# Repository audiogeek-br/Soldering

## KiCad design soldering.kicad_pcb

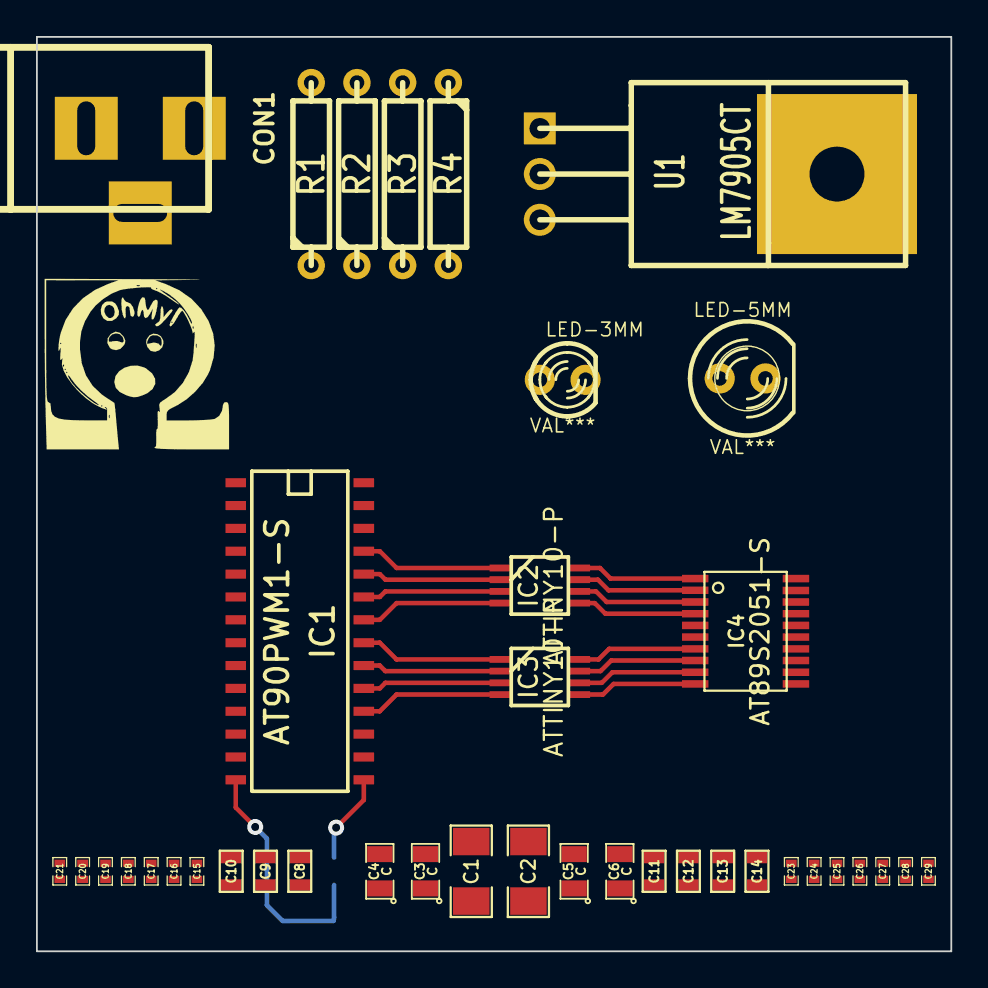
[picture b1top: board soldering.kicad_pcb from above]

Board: 2 copper layers, 50.8 x 50.8 mm, 40 parts (1 on the bottom side), 18 nets.

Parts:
C1, C2: C; SM1206
C3, C4, C5, C6: C; SM0805
C7, C8, C9, C10, C11, C12, C13, C14: C; SM0603
C15, C16, C17, C18, C19, C20, C21, C23, C24, C25, C26, C27, C28, C29: C; SM0402
CON1: BARREL_JACK
IC1: AT90PWM1-S; S0IC28N
IC2, IC3: ATTINY10-P; MSOP_8
IC4: AT89S2051-S; tssop-20
LED-3MM: VAL***; LED-3MM
LED-5MM: VAL***; LED-5MM
R1, R2, R3, R4: R; R4
U1: LM7905CT; LM79XX

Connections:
GND: CON1.2, CON1.3, R1.2, R2.1, R2.2, R3.1, R3.2, R4.2
unnamed: IC2.8, IC4.1
unnamed: IC3.8, IC4.7
unnamed: IC2.7, IC4.2
unnamed: IC2.6, IC4.3
unnamed: IC2.5, IC4.4
unnamed: IC1.21, IC3.1
unnamed: IC1.24, IC2.2
unnamed: IC1.22, IC2.4
unnamed: IC1.23, IC2.3
unnamed: IC1.20, IC3.2
unnamed: IC1.19, IC3.3
unnamed: IC1.18, IC3.4
unnamed: C7.2, IC1.14
unnamed: C7.1, IC1.15
unnamed: IC3.7, IC4.8
unnamed: IC3.6, IC4.9
unnamed: IC3.5, IC4.10

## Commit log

2014-01-24 First ideas.
2014-01-24 Added a screenshot.
2014-01-29 Added an LED, via, and Logo
2014-02-02 Added another WIP pic.
